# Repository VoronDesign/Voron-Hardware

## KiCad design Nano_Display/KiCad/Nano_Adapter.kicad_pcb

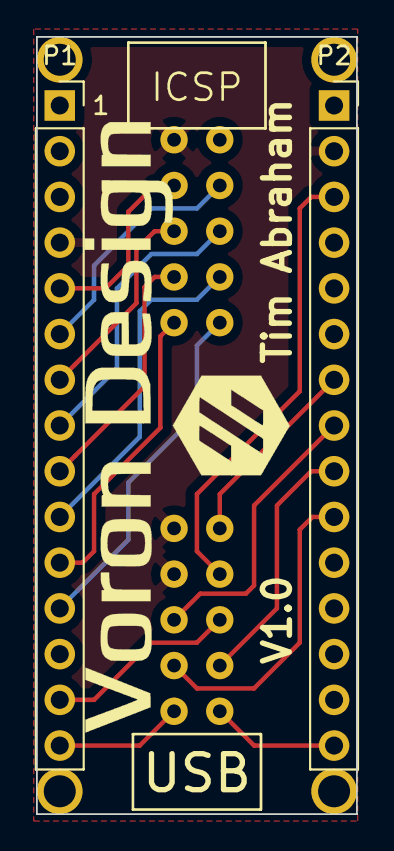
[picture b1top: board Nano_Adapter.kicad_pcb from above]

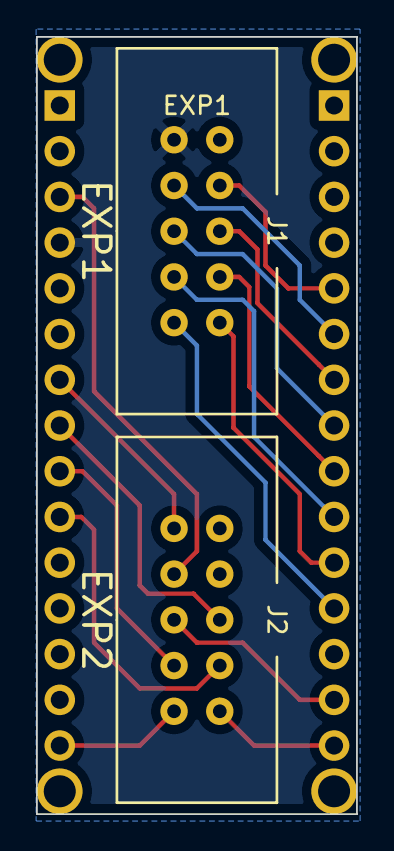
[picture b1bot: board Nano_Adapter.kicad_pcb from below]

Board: 2 copper layers, 17.8 x 43.2 mm, 8 parts (2 on the bottom side), 18 nets.

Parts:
J1: EXP1; Shrouded_2x5_pin_header
J2: EXP2; Shrouded_2x5_pin_header
P1: Digital; PinSocket_1x15_P2.54mm_Vertical
P2: Analog; PinSocket_1x15_P2.54mm_Vertical
P3, P4, P5, P6: CONN_01X01; 1pin_Nano

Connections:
+5V: J1.10, P2.4
/2: J1.7, P1.5
/3(**): J1.8, P1.6
/4: J1.5, P1.7
/5(**): J1.6, P1.8
/6(**): J1.3, P1.9
/7: J1.4, P1.10
/8: J1.1, P1.11
/9(**): J1.2, P1.12
/11(**/MOSI): J2.6, P1.14
/12(MISO): J2.1, P1.15
/13(SCK): J2.2, P2.15
/A2: J2.3, P2.10
/A3: J2.4, P2.9
/A4: J2.5, P2.8
/A5: J2.10, P2.7
/Reset: J2.8, P2.3
GND: J1.9, J2.7, J2.9, P1.4, P2.2

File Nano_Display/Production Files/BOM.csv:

"Id";"Designator";"Package";"Quantity";"Description";"Link 1";"Link 2"
1;"J1,J2";"Shrouded_2x5_pin_header";2;"2x5 pin IDC header 2.54mm Shielded";"https://www.mouser.com/ProductDetail/Wurth-Elektronik/61201021621";"https://www.amazon.com/HONJIE-10Pins-Straight-Connector-Head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"
2;"P1,P2";"PinSocket_1x15_P2.54mm_Vertical";2;"2.54mm male header pin 15 pin ";"https://www.mouser.com/ProductDetail/Gravitech/15Fx1-254mm";"https://www.amazon.com/2-54mm-Female-Single-Straight-Header/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"

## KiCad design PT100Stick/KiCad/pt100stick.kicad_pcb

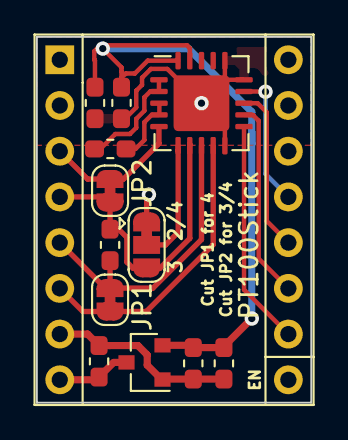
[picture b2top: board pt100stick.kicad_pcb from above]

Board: 2 copper layers, 15.2 x 20.3 mm, 13 parts (0 on the bottom side), 14 nets.

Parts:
A1: Pololu_Breakout_A4988; Pololu_Breakout-16_15.2x20.3mm
C1, C2, C3, C4, C5: 0.1uF; C_0603_1608Metric_Pad1.05x0.95mm_HandSolder
C6: 2.2uF; C_0603_1608Metric_Pad1.05x0.95mm_HandSolder
JP1: Cut for 4; SolderJumper-2_P1.3mm_Bridged_RoundedPad1.0x1.5mm
JP2: Cut for 3/4; SolderJumper-2_P1.3mm_Bridged_RoundedPad1.0x1.5mm
JP3: SolderJumper_3_Bridged12; SolderJumper-3_P1.3mm_Bridged12_RoundedPad1.0x1.5mm
R1: 402; R_0603_1608Metric_Pad1.05x0.95mm_HandSolder
U1: MAX31865ATP_; TQFN-20-1EP_5x5mm_P0.65mm_EP3.1x3.1mm
U2: MCP1799T-3302H; SOT-23

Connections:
+3V3: C2.1, C3.1, C5.1, C6.1, U1.19, U1.20, U2.2
+24V: A1.8, C4.1, U2.3
/BIAS: R1.2, U1.1, U1.2
/CS: A1.12, U1.13
/FORCE2: JP3.2, U1.6
/FORCE+: A1.3, JP2.1, U1.5
/FORCE-: A1.6, JP1.1, U1.9
/MISO: A1.10, U1.11
/MOSI: A1.13, U1.14
/RTDIN+: A1.4, C1.1, JP2.2, JP3.3, U1.7
/RTDIN-: A1.5, C1.2, JP1.2, U1.8
/SCK: A1.11, U1.12
GND: A1.7, C2.2, C3.2, C4.2, C5.2, C6.2, JP3.1, U1.10, U1.15, U1.16, U1.21, U2.1
unnamed: R1.1, U1.3, U1.4

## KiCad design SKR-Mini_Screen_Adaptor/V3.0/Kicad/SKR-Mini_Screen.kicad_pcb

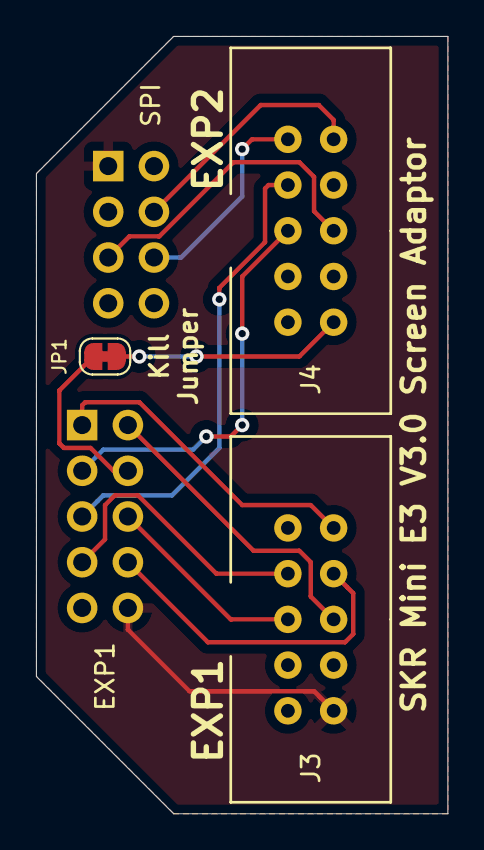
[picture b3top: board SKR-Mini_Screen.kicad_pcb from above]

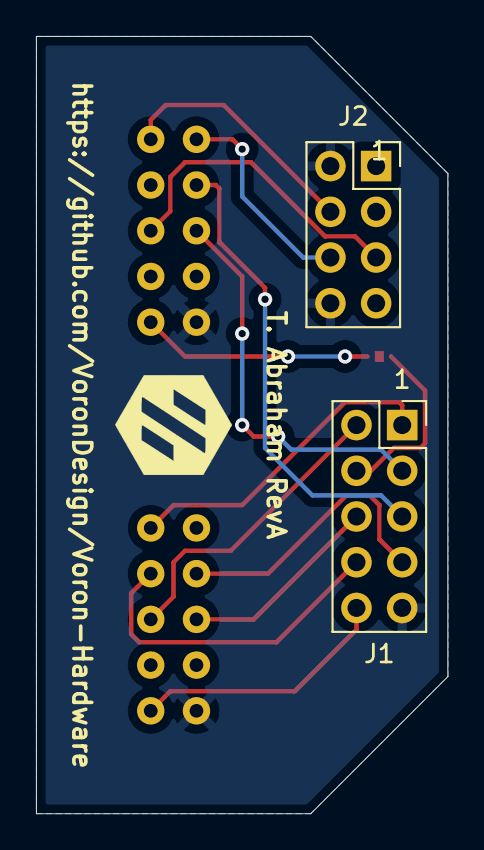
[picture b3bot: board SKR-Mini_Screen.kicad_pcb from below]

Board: 2 copper layers, 22.9 x 43.2 mm, 5 parts (2 on the bottom side), 14 nets.

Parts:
J1: Board_EXP1; PinSocket_2x05_P2.54mm_Vertical
J2: Board_SPI; PinSocket_2x04_P2.54mm_Vertical
J3: Screen_EXP1; Shrouded_2x5_pin_header
J4: Screen_EXP2; Shrouded_2x5_pin_header
JP1: Jumper_NC_Small; SolderJumper-2_P1.3mm_Bridged_RoundedPad1.0x1.5mm

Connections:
/+5V: J1.10, J2.1, J3.10
/GND: J1.9, J2.2, J2.8, J3.9, J4.9
/Kill: J4.10, JP1.2
/MISO: J2.6, J4.1
/MOSI: J2.5, J4.6
/PA9: J1.3, J4.5
/PA10: J1.5, J4.3
/PA15: J1.2, J3.6
/PB5: J1.1, J3.2
/PB8: J1.7, J3.3
/PB9: J1.6, J3.5
/PB15: J1.8, J3.4
/RST: J1.4, JP1.1
/SCK: J2.4, J4.2

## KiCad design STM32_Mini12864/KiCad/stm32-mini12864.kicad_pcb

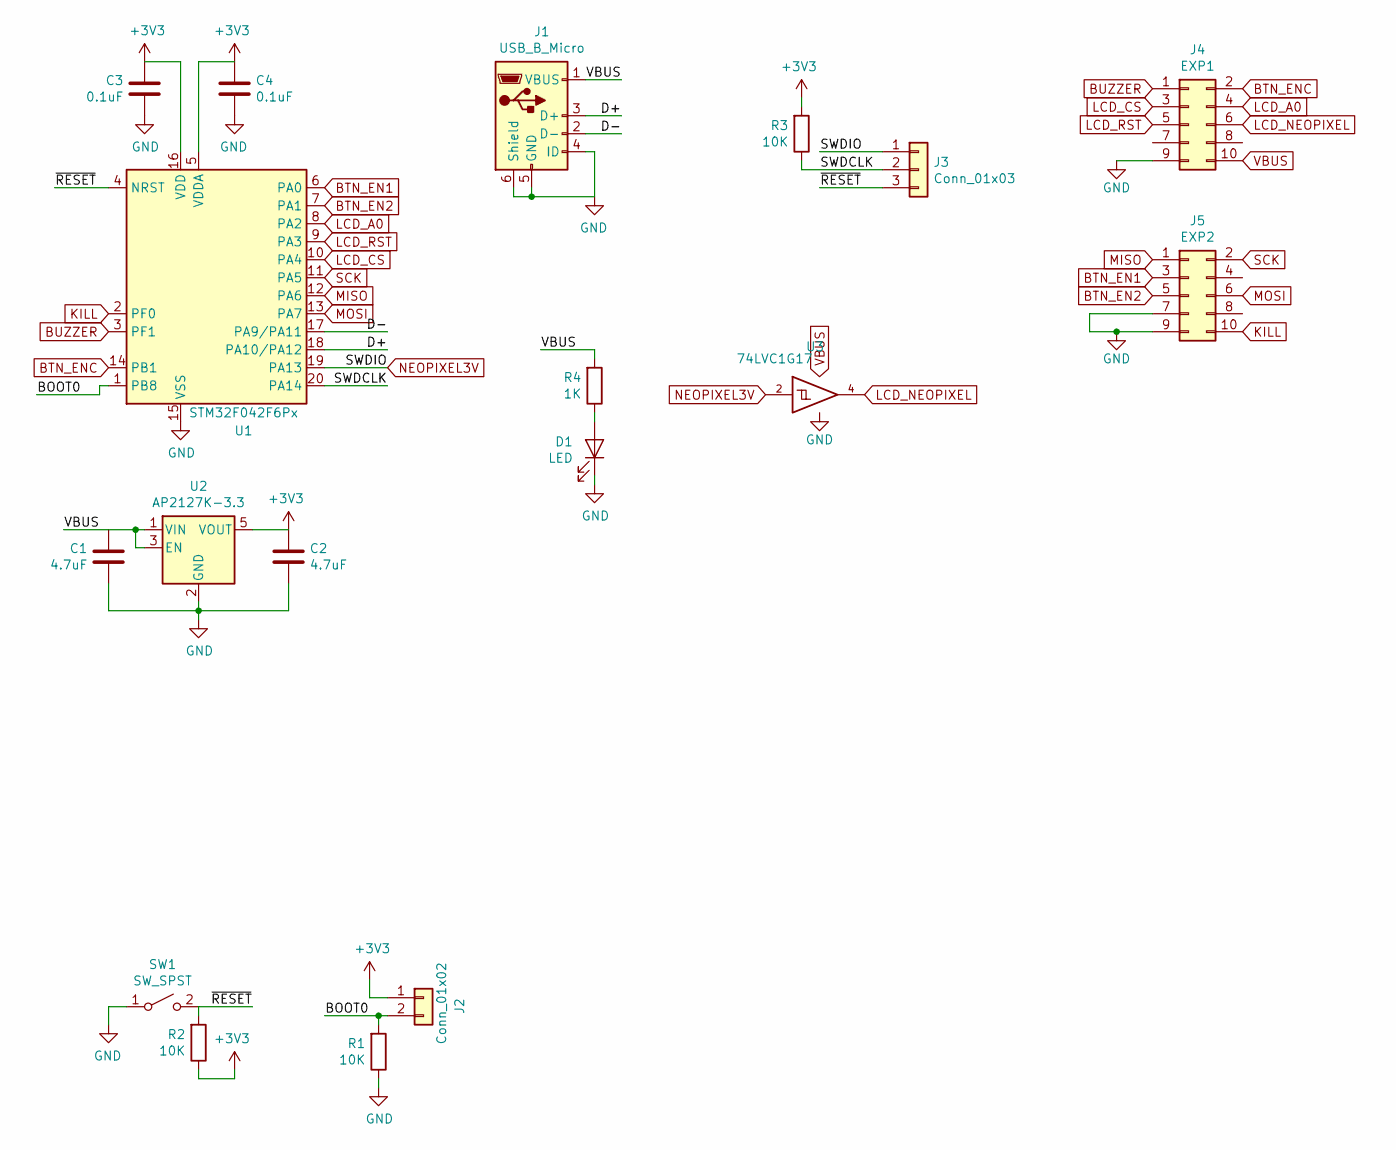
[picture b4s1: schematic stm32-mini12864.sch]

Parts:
C1, C2: 4.7uF; C_0805_2012Metric; MPN CC0805KKX5R8BB475; LCSC C1779
C3, C4: 0.1uF; C_0805_2012Metric; MPN CC0805KRX7R9BB104; LCSC C49678
D1: LED; LED_0805_2012Metric; MPN 17-215SURC/S530-A2/TR8; LCSC C84256
J1: USB_B_Micro; Molex-105017-0001-USBMicroB; MPN 1050170001
J2: Conn_01x02; PinHeader_1x02_P2.54mm_Vertical
J3: Conn_01x03; PinHeader_1x03_P2.54mm_Vertical
J4: EXP1; PinHeader_2x05_P2.54mm_Vertical_SMD_alt
J5: EXP2; PinHeader_2x05_P2.54mm_Vertical_SMD_alt
R1, R2, R3: 10K; R_0805_2012Metric; MPN RC0805JR-0710KL; LCSC C17414
R4: 1K; R_0805_2012Metric; MPN RC0805JR-071KL; LCSC C17513
SW1: SW_SPST; 2PinTactileButton
U1: STM32F042F6Px; TSSOP-20_4.4x6.5mm_P0.65mm; MPN STM32F042F6P6; LCSC C81000
U2: AP2127K-3.3; SOT-23-5; MPN AP2127K-3.3TRG1; LCSC C156285
U3: 74LVC1G17; SOT-753

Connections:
+3V3: C2.2, C3.2, C4.2, J2.1, R2.1, R3.2, U1.5 (VDDA), U1.16 (VDD), U2.5 (VOUT)
/BOOT0: J2.2, R1.2, U1.1 (PB8)
/D+: J1.3 (D+), U1.18 (PA10/PA12)
/D-: J1.2 (D-), U1.17 (PA9/PA11)
/SWDCLK: J3.2, R3.1, U1.20 (PA14)
/~RESET: J3.3, R2.2, SW1.2 (B), U1.4 (NRST)
BTN_EN1: J5.3, U1.6 (PA0)
BTN_EN2: J5.5, U1.7 (PA1)
BTN_ENC: J4.2, U1.14 (PB1)
BUZZER: J4.1, U1.3 (PF1)
GND: C1.1, C2.1, C3.1, C4.1, D1.1 (K), J1.4 (ID), J1.5 (GND), J1.6 (Shield), J4.9, J5.7, J5.9, R1.1, SW1.1 (A), U1.15 (VSS), U2.2 (GND), U3.3 (GND)
KILL: J5.10, U1.2 (PF0)
LCD_A0: J4.4, U1.8 (PA2)
LCD_CS: J4.3, U1.10 (PA4)
LCD_NEOPIXEL: J4.6, U3.4
LCD_RST: J4.5, U1.9 (PA3)
MISO: J5.1, U1.12 (PA6)
MOSI: J5.6, U1.13 (PA7)
NEOPIXEL3V: J3.1, U1.19 (PA13), U3.2
unnamed: D1.2 (A), R4.1
SCK: J5.2, U1.11 (PA5)
VBUS: C1.2, J1.1 (VBUS), J4.10, R4.2, U2.1 (VIN), U2.3 (EN), U3.5 (VCC)

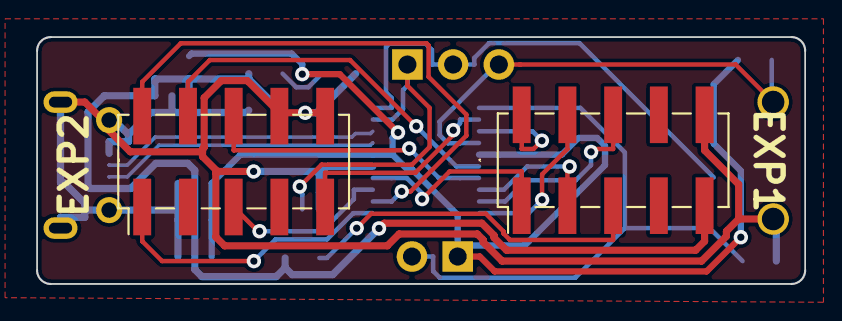
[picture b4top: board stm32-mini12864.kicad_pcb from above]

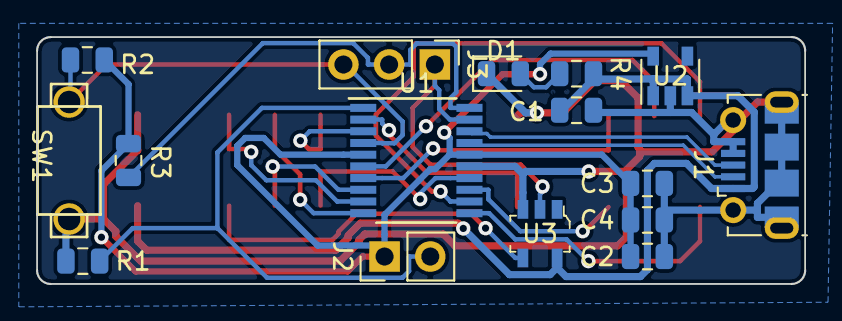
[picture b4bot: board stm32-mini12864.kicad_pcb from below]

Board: 2 copper layers, 42.7 x 13.7 mm, 18 parts (16 on the bottom side), 22 nets.

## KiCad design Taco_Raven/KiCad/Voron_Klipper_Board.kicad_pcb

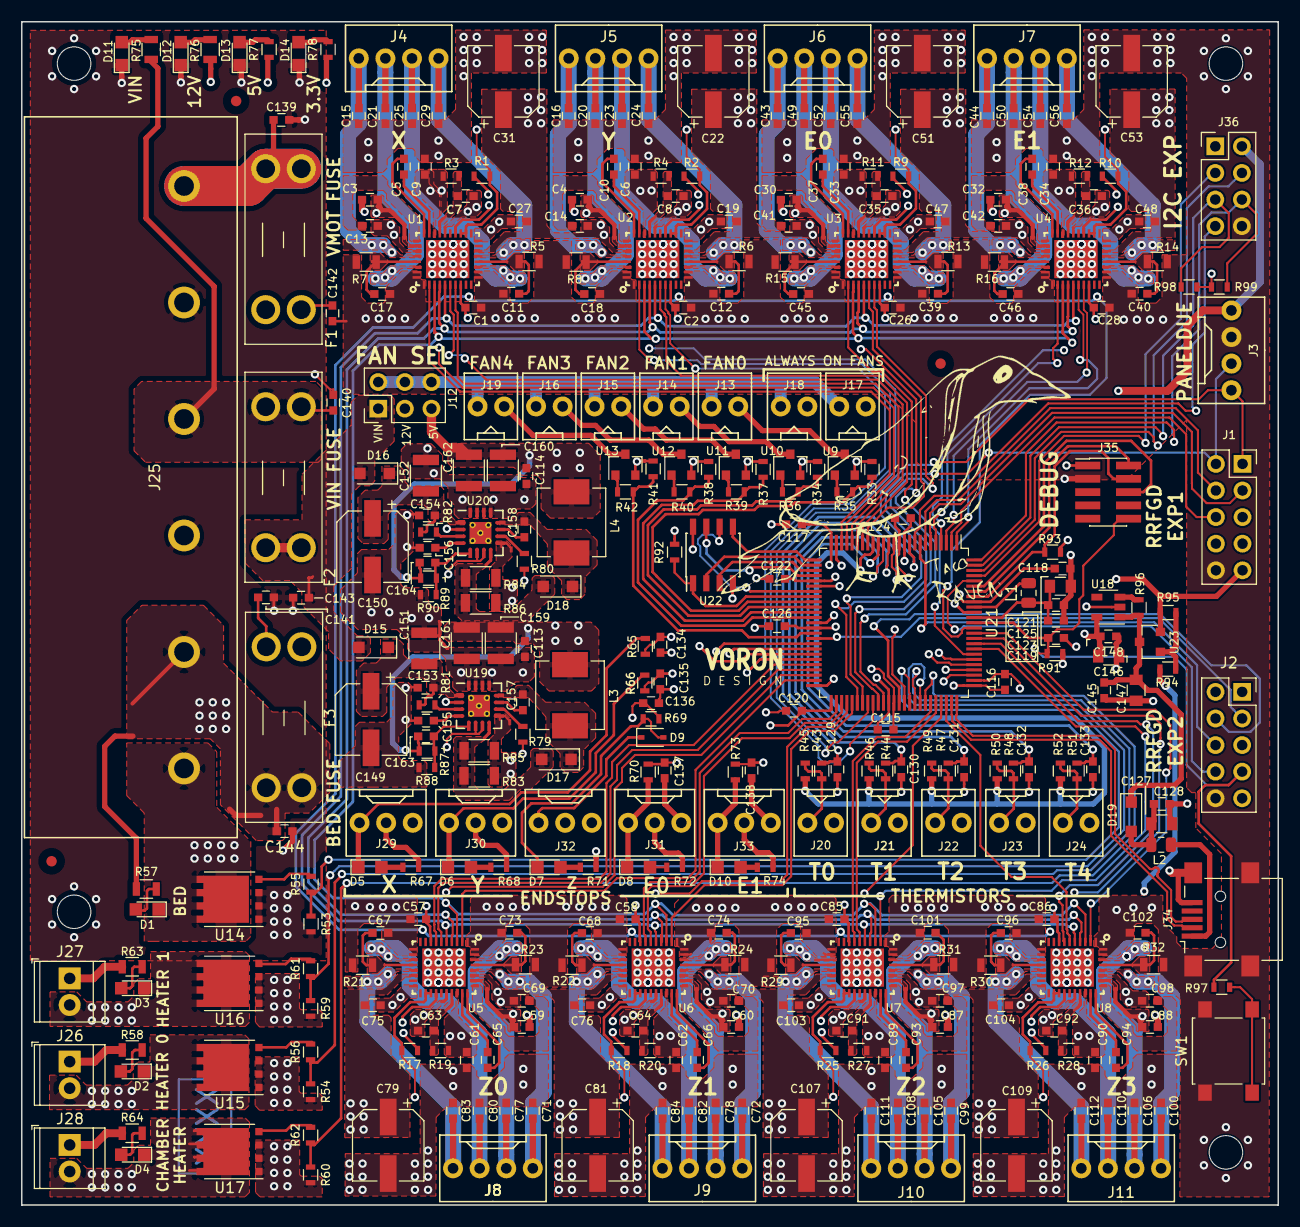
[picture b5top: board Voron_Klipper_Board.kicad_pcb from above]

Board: 4 copper layers, 120.0 x 113.0 mm, 357 parts (0 on the bottom side), 238 nets.

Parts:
C1, C2, C3, C4, C5, C6, C7, C8, C11, C12, C13, C14, C17, C18, C19, C26, C27, C28, C30, C32, C33, C34, C35, C36, C39, C40, C41, C42, C45, C46, C47, C48, C57, C58, C59, C60, C61, C62, C63, C64, C67, C68, C69, C70, C73, C74, C75, C76, C85, C86, C87, C88, C89, C90, C91, C92, C95, C96, C97, C98, C101, C102, C103, C104, C113, C114, C115, C116, C117, C118, C119, C120, C122, C124, C125, C126, C139, C140, C141, C142, C143, C144, C153, C154, C155, C156: 100nF; C_0603
C9, C10, C37, C38, C65, C66, C93, C94, C157, C158: 22nF; C_0603
C15, C16, C20, C21, C23, C24, C25, C29, C43, C44, C49, C50, C52, C54, C55, C56, C71, C72, C77, C78, C80, C82, C83, C84, C99, C100, C105, C106, C108, C110, C111, C112: 1nF; C_0603
C22, C31, C51, C53, C79, C81, C107, C109, C149, C150: 100uF; CP_Elec_6.3x7.7
C121, C127, C146, C147: 10uF; C_0805
C123, C128, C145, C148: 1uF; C_0603
C129, C130, C131, C132, C133, C134, C135, C136, C137, C138: 2.2uF; C_0603
C151, C152, C159, C160, C161, C162: 10uF; C_1210
C163: 8.2nF; C_0603
C164: 10nF; C_0603
D1, D2, D3, D4, D5, D6, D7, D8, D10: Red; LED_0805
D9: BAT43; D_SOD-323
D11, D12, D13, D14: Blue; LED_0805
D15, D16, D17, D18, D19: DB2W40300L; D_SOD-123F
F1, F2, F3: 3557-2; Fuseholder_Blade_Mini_Keystone_3568
FID1, FID2, FID3: FIDUCIAL_1MM; Fiducial_1mm_Dia_2.54mm_Outer_CopperBottom
G2: mzbot; LOGO
J1, J2: CONN_02X05; PinSocket_2x05_P2.54mm_Vertical
J3, J4, J5, J6, J7, J8, J9, J10, J11: CONN_01X04; Molex_KK_1X4
J12: CONN_02X03; PinHeader_2x03_P2.54mm_Vertical
J13, J14, J15, J16, J17, J18, J19, J20, J21, J22, J23, J24: CONN_01X02; Molex_KK_1X2
J25: CONN_01X06; 8PCV-06-006
J26, J27, J28: CONN_01X02; TerminalBlock_TE_282834-2_1x02_P2.54mm_Horizontal
J29, J30, J31, J32, J33: CONN_01X03; Molex_KK_1X3
J34: USB_MINI; USB_Mini-B_Lumberg_2486_01_Horizontal
J35: CONN_02X05; PinHeader_2x05_P1.27mm_Vertical_SMD
J36: CONN_02X04; PinHeader_2x04_P2.54mm_Vertical
L1: 10uH; L_0805_2012Metric
L2: Ferrite_0805; L_0805_2012Metric
L3, L4: 10uH; L_Vishay_IHLP-2525
MH1, MH2, MH3, MH4: MountingHole; MountingHole_3.2mm_M3_DIN965
R1, R2, R9, R10, R17, R18, R25, R26, R33, R34, R37, R38, R41, R53, R54, R59, R60, R65, R66, R69, R70, R73, R91, R92, R93: 10.0K; R_0603
R3, R4, R11, R12, R19, R20, R27, R28: 10R; R_0603
R5, R6, R7, R8, R13, R14, R15, R16, R21, R22, R23, R24, R29, R30, R31, R32: 0R11; R_0805
R35, R36, R39, R40, R42, R43, R44, R47, R48, R51, R67, R68, R71, R72, R74, R77: 1.00K; R_0603
R45, R46, R49, R50, R52, R98, R99: 4.70K; R_0603
R55, R56, R61, R62, R78: 180; R_0603
R57, R58, R63, R64, R75, R76: 6.80K; R_0805
R79, R80: 0R; R_0603
R81: 200K; R_0603
R82, R94, R95, R96: 100K; R_0603
R83, R85: 0.10; R_1206
R84, R86: 0.130; R_1206
R87: 10.5K; R_0603
R88: 750; R_0603
R89: 3.48K; R_0603
R90: 681; R_0603
R97: 330; R_0603
SW1: SW_Push; SW_SPST_B3S-1000
U1, U2, U3, U4, U5, U6, U7, U8: TMC2130; QFN36_0.5_5.0X6.0
U9, U10, U11, U12, U13, U23: PMV40UN; SOT-23
U14, U15, U16, U17: CSD18532; VSONP-8-1EP_5x6_P1.27mm
U18: AP2112-3.3; SOT-23-5
U19, U20: A4403; WQFN-16-1EP_4x4mm_P0.65mm_EP2.1x2.1mm_ThermalVias
U21: ATSAMD51; TQFP-100_14x14mm_P0.5mm
U22: SPIFLASH_SOIC8; SOIC-8_3.9x4.9mm_Pitch1.27mm

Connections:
+3.3V: C1.2, C2.2, C26.2, C28.2, C57.2, C58.2, C85.2, C86.2, C115.2, C116.2, C117.2, C118.2, C120.2, C122.2, C124.2, C126.2, C146.2, C148.2, J29.2, J30.2, J31.2, J33.2, J35.1, J36.1, R1.1, R2.1, R9.1, R10.1, R17.1, R18.1, R25.1, R26.1, R67.2, R68.2, R71.2, R72.2, R74.2, R78.1, R91.1, R92.1, R93.1, R98.1, R99.1, U1.8, U2.8, U3.8, U4.8, U5.8, U6.8, U7.8, U8.8, U18.5, U21.12, U21.25, U21.30, U21.39, U21.51, U21.63, U21.77, U21.92, U22.8
+5V: C3.2, C4.2, C5.2, C6.2, C30.2, C32.2, C33.2, C34.2, C59.2, C60.2, C61.2, C62.2, C87.2, C88.2, C89.2, C90.2, C114.2, C160.1, C162.1, C164.2, J1.9, J3.4, J12.5, J36.2, L4.2, R3.1, R4.1, R11.1, R12.1, R19.1, R20.1, R27.1, R28.1, R77.1, R89.1, R95.1, U1.26, U1.30, U2.26, U2.30, U3.26, U3.30, U4.26, U4.30, U5.26, U5.30, U6.26, U6.30, U7.26, U7.30, U8.26, U8.30, U23.2
+12V: C113.2, C159.1, C161.1, C163.2, J12.3, J32.2, L3.2, R76.1, R87.1, R94.2
+VIN: C140.2, C141.2, F2.1, F3.1, J25.3, R75.1
+VIN_FUSED: C143.2, D15.2, D16.2, F2.2, J12.1, J26.1, J27.1, J28.1, R58.1, R63.1, R64.1
+V_FAN: J12.2, J12.4, J12.6, J13.2, J14.2, J15.2, J16.2, J17.2, J18.2, J19.2
BED: R53.1, R55.1, U21.66
BED_SWITCH: D1.1, J25.6, U14.3
D+: J34.3, U21.75
D-: J34.2, U21.74
DIAG_E0: R9.2, U3.20, U3.21, U21.61
DIAG_E1: R10.2, U4.20, U4.21, U21.4
DIAG_X: R1.2, U1.20, U1.21, U21.22
DIAG_Y: R2.2, U2.20, U2.21, U21.58
DIAG_Z0: R17.2, U5.20, U5.21, U21.48
DIAG_Z1: R18.2, U6.20, U6.21, U21.54
DIAG_Z2: R25.2, U7.20, U7.21, U21.72
DIAG_Z3: R26.2, U8.20, U8.21, U21.85
DIR_E0: U3.7, U21.60
DIR_E1: U4.7, U21.3
DIR_X: U1.7, U21.21
DIR_Y: U2.7, U21.45
DIR_Z0: U5.7, U21.46
DIR_Z1: U6.7, U21.52
DIR_Z2: U7.7, U21.70
DIR_Z3: U8.7, U21.84
E0_OA1: C49.2, J6.3, U3.34
E0_OA2: C43.2, J6.4, U3.32
E0_OB1: C52.2, J6.2, U3.13
E0_OB2: C55.2, J6.1, U3.15
E1_OA1: C50.2, J7.3, U4.34
E1_OA2: C44.2, J7.4, U4.32
E1_OB1: C54.2, J7.2, U4.13
E1_OB2: C56.2, J7.1, U4.15
ENDSTOP_E0: C137.2, R70.2, U21.80
ENDSTOP_E1: C138.2, R73.2, U21.81
ENDSTOP_X: C134.2, R65.2, U21.65
ENDSTOP_Y: C135.2, R66.2, U21.78
EXP_I2C_INT: J36.4, U21.98
EXP_I2C_OSCK: J36.3, U21.97
EXP_I2C_RST: J36.7, U21.9
EXP_I2C_SCL: J36.6, R99.2, U21.100
EXP_I2C_SDA: J36.5, R98.2, U21.99
FAN0: R33.1, R35.2, U21.34
FAN1: R34.1, R36.2, U21.35
FAN2: R37.1, R39.2, U21.36
FAN3: R38.1, R40.2, U21.37
FAN4: R41.1, R42.2, U21.40
FLASH_CS: R92.2, U21.33, U22.1
FLASH_IO0: U21.26, U22.5
FLASH_IO1: U21.27, U22.2
FLASH_IO2: U21.28, U22.3
FLASH_IO3: U21.29, U22.7
FLASH_SCK: U21.32, U22.6
GND: C1.1, C2.1, C3.1, C4.1, C5.1, C6.1, C7.1, C8.1, C11.1, C12.1, C15.1, C16.1, C17.1, C18.1, C19.1, C20.1, C21.1, C22.2, C23.1, C24.1, C25.1, C26.1, C27.1, C28.1, C29.1, C30.1, C31.2, C32.1, C33.1, C34.1, C35.1, C36.1, C39.1, C40.1, C43.1, C44.1, C45.1, C46.1, C47.1, C48.1, C49.1, C50.1, C51.2, C52.1, C53.2, C54.1, C55.1, C56.1, C57.1, C58.1, C59.1, C60.1, C61.1, C62.1, C63.1, C64.1, C67.1, C68.1, C71.1, C72.1, C73.1, C74.1, C75.1, C76.1, C77.1, C78.1, C79.2, C80.1, C81.2, C82.1, C83.1, C84.1, C85.1, C86.1, C87.1, C88.1, C89.1, C90.1, C91.1, C92.1, C95.1, C96.1, C99.1, C100.1, C101.1, C102.1, C103.1, C104.1, C105.1, C106.1, C107.2, C108.1, C109.2, C110.1, C111.1, C112.1, C113.1, C114.1, C115.1, C116.1, C117.1, C118.1, C119.1, C120.1, C121.1, C122.1, C123.1, C124.1, C125.1, C126.1, C127.1, C128.1, C129.1, C130.1, C131.1, C132.1, C133.1, C134.1, C135.1, C136.1, C137.1, C138.1, C139.1, C140.1, C141.1, C142.1, C143.1, C144.1, C145.1, C146.1, C147.1, C148.1, C149.2, C150.2, C151.2, C152.2, C153.1, C154.1, C155.1, C156.1, C159.2, C160.2, C161.2, C162.2, D11.1, D12.1, D13.1, D14.1, J1.10, J2.10, J3.3, J17.1, J18.1, J20.2, J21.2, J22.2, J23.2, J24.2, J25.2, J25.4, J29.3, J30.3, J31.3, J32.3, J33.3, J34.5, J34.6, J35.3, J36.8, R5.2, R6.2, R7.2, R8.2, R13.2, R14.2, R15.2, R16.2, R21.2, R22.2, R23.2, R24.2, R29.2, R30.2, R31.2, R32.2, R33.2, R34.2, R37.2, R38.2, R41.2, R53.2, R54.2, R59.2, R60.2, R79.2, R80.2, R83.2, R84.2, R85.2, R86.2, R88.2, R90.2, SW1.1, U1.1, U1.11, U1.12, U1.18, U1.24, U1.35, U1.36, U1.37, U2.1, U2.11, U2.12, U2.18, U2.24, U2.35, U2.36, U2.37, U3.1, U3.11, U3.12, U3.18, U3.24, U3.35, U3.36, U3.37, U4.1, U4.11, U4.12, U4.18, U4.24, U4.35, U4.36, U4.37, U5.1, U5.11, U5.12, U5.18, U5.24, U5.35, U5.36, U5.37, U6.1, U6.11, U6.12, U6.18, U6.24, U6.35, U6.36, U6.37, U7.1, U7.11, U7.12, U7.18, U7.24, U7.35, U7.36, U7.37, U8.1, U8.11, U8.12, U8.18, U8.24, U8.35, U8.36, U8.37, U9.2, U10.2, U11.2, U12.2, U13.2, U14.1, U15.1, U16.1, U17.1, U18.2, U19.2, U19.6, U19.7, U19.9, U19.13, U19.14, U19.15, U19.16, U19.17, U20.2, U20.6, U20.7, U20.9, U20.13, U20.14, U20.15, U20.16, U20.17, U21.11, U21.24, U21.31, U21.38, U21.50, U21.62, U21.76, U21.90, U22.4
HEATED_CHAMBER: R60.1, R62.1, U21.69
HOTEND0: R54.1, R56.1, U21.67
HOTEND1: R59.1, R61.1, U21.68
unnamed: C7.2, R3.2, U1.25
unnamed: C8.2, R4.2, U2.25
unnamed: C9.1, U1.28
unnamed: C9.2, U1.27
unnamed: C10.1, U2.28
unnamed: C10.2, U2.27
unnamed: C11.2, R5.1, U1.14
unnamed: C12.2, R6.1, U2.14
unnamed: C13.1, U1.29
unnamed: C14.1, U2.29
unnamed: C17.2, R7.1, U1.33
unnamed: C18.2, R8.1, U2.33
unnamed: C35.2, R11.2, U3.25
unnamed: C36.2, R12.2, U4.25
unnamed: C37.1, U3.28
unnamed: C37.2, U3.27
unnamed: C38.1, U4.28
unnamed: C38.2, U4.27
unnamed: C39.2, R13.1, U3.14
unnamed: C40.2, R14.1, U4.14
unnamed: C41.1, U3.29
unnamed: C42.1, U4.29
unnamed: C45.2, R15.1, U3.33
unnamed: C46.2, R16.1, U4.33
unnamed: C63.2, R19.2, U5.25
unnamed: C64.2, R20.2, U6.25
unnamed: C65.1, U5.28
unnamed: C65.2, U5.27
unnamed: C66.1, U6.28
unnamed: C66.2, U6.27
unnamed: C67.2, R21.1, U5.14
unnamed: C68.2, R22.1, U6.14
unnamed: C69.1, U5.29
unnamed: C70.1, U6.29
unnamed: C73.2, R23.1, U5.33
unnamed: C74.2, R24.1, U6.33
unnamed: C91.2, R27.2, U7.25
unnamed: C92.2, R28.2, U8.25
unnamed: C93.1, U7.28
unnamed: C93.2, U7.27
unnamed: C94.1, U8.28
unnamed: C94.2, U8.27
unnamed: C95.2, R29.1, U7.14
unnamed: C96.2, R30.1, U8.14
unnamed: C97.1, U7.29
unnamed: C98.1, U8.29
unnamed: C101.2, R31.1, U7.33
unnamed: C102.2, R32.1, U8.33
unnamed: C121.2, C123.2, C125.2, L1.1, U21.89
unnamed: C145.2, C147.2, D19.1, R96.2, U18.1, U23.3
unnamed: C149.1, C151.1, C153.2, D15.1, R81.1, U19.1
unnamed: C150.1, C152.1, C154.2, D16.1, R82.1, U20.1
unnamed: C155.2, U19.4
unnamed: C156.2, U20.4
unnamed: C157.1, U19.11
unnamed: C157.2, D17.1, L3.1, U19.12
unnamed: C158.1, U20.11
unnamed: C158.2, D18.1, L4.1, U20.12
unnamed: C163.1, R87.2, R88.1, U19.5
unnamed: C164.1, R89.2, R90.1, U20.5
unnamed: D1.2, R57.2
unnamed: D2.1, J26.2, U15.3
unnamed: D2.2, R58.2
unnamed: D3.1, J27.2, U16.3
unnamed: D3.2, R63.2
unnamed: D4.1, J28.2, U17.3
unnamed: D4.2, R64.2
unnamed: D5.1, J29.1, R65.1
unnamed: D5.2, R67.1
unnamed: D6.1, J30.1, R66.1
unnamed: D6.2, R68.1
unnamed: D7.1, D9.2, R69.1
unnamed: D7.2, R71.1
unnamed: D8.1, J31.1, R70.1
unnamed: D8.2, R72.1
unnamed: D9.1, J32.1
unnamed: D10.1, J33.1, R73.1
unnamed: D10.2, R74.1
unnamed: D11.2, R75.2
unnamed: D12.2, R76.2
unnamed: D13.2, R77.2
unnamed: D14.2, R78.2
unnamed: D17.2, R83.1, R85.1, U19.8
unnamed: D18.2, R84.1, R86.1, U20.8
unnamed: J13.1, U9.3
unnamed: J14.1, U10.3
unnamed: J15.1, U11.3
unnamed: J16.1, U12.3
unnamed: J19.1, U13.3
unnamed: J20.1, R43.1, R45.2
unnamed: J21.1, R44.1, R46.2
unnamed: J22.1, R47.1, R49.2
unnamed: J23.1, R48.1, R50.2
unnamed: J24.1, R51.1, R52.2
unnamed: J34.1, L2.1
unnamed: L1.2, U21.91
unnamed: R35.1, U9.1
unnamed: R36.1, U10.1
unnamed: R39.1, U11.1
unnamed: R40.1, U12.1
unnamed: R42.1, U13.1
unnamed: R55.2, U14.2
unnamed: R56.2, U15.2
unnamed: R61.2, U16.2
unnamed: R62.2, U17.2
unnamed: R79.1, U19.10
unnamed: R80.1, U20.10
unnamed: R81.2, U19.3
unnamed: R82.2, U20.3
unnamed: R94.1, R95.2, U23.1
unnamed: R96.1, U18.3
unnamed: R97.2, SW1.2
PD_RX_RRFGD_BUZ: J1.2, J3.2, U21.56
PD_TX_RRFGD_BTN_ENC: J1.1, J3.1, U21.57
RESETN: C119.2, J2.7, J35.10, R91.2, R97.1, U21.88
RRFGD_BTN_EN1: J2.4, U21.64
RRFGD_BTN_EN2: J2.6, U21.8
RRFGD_LCD4: J1.6, U21.2
RRFGD_LCDE: J1.4, U21.7
RRFGD_LCDRS: J1.3, U21.6
RRFGD_SDCSEL: J2.3, U21.41
RRFGD_SDDET: J2.8, U21.96
SPI_CLK: J2.1, U1.3, U2.3, U3.3, U4.3, U5.3, U6.3, U7.3, U8.3, U21.43
SPI_CS_E0: U3.2, U21.82
SPI_CS_E1: U4.2, U21.5
SPI_CS_X: U1.2, U21.23
SPI_CS_Y: U2.2, U21.59
SPI_CS_Z0: U5.2, U21.49
SPI_CS_Z1: U6.2, U21.55
SPI_CS_Z2: U7.2, U21.83
SPI_CS_Z3: U8.2, U21.86
SPI_SDI: J2.2, U1.4, U2.4, U3.4, U4.4, U5.4, U6.4, U7.4, U8.4, U21.42
SPI_SDO: J2.5, U1.5, U2.5, U3.5, U4.5, U5.5, U6.5, U7.5, U8.5, U21.44
STEP_E0: U3.6, U21.18
STEP_E1: U4.6, U21.1
STEP_X: U1.6, U21.20
STEP_Y: U2.6, U21.19
STEP_Z0: U5.6, U21.47
STEP_Z1: U6.6, U21.53
STEP_Z2: U7.6, U21.71
STEP_Z3: U8.6, U21.73
SWCLK: J35.4, R93.2, U21.93
SWDIO: J35.2, U21.94
SWO: J35.6, U21.95
T0: C129.2, R43.2, U21.10
T1: C130.2, R44.2, U21.13
T2: C131.2, R47.2, U21.14
T3: C132.2, R48.2, U21.15
T4: C133.2, R51.2, U21.16
TMC_EN: U1.22, U2.22, U3.22, U4.22, U5.22, U6.22, U7.22, U8.22, U21.87
VBED_FUSED: C144.2, F3.2, J25.5, R57.1
VBUS: C127.2, C128.2, D19.2, L2.2
VMOT: C139.2, F1.1, J25.1
VMOT_FUSED: C13.2, C14.2, C19.2, C22.1, C27.2, C31.1, C41.2, C42.2, C47.2, C48.2, C51.1, C53.1, C69.2, C70.2, C75.2, C76.2, C79.1, C81.1, C97.2, C98.2, C103.2, C104.2, C107.1, C109.1, C142.2, F1.2, U1.16, U1.31, U2.16, U2.31, U3.16, U3.31, U4.16, U4.31, U5.16, U5.31, U6.16, U6.31, U7.16, U7.31, U8.16, U8.31
VREF: R45.1, R46.1, R49.1, R50.1, R52.1, U21.17
X_OA1: C21.2, J4.3, U1.34
X_OA2: C15.2, J4.4, U1.32
X_OB1: C25.2, J4.2, U1.13
X_OB2: C29.2, J4.1, U1.15
Y_OA1: C20.2, J5.3, U2.34
Y_OA2: C16.2, J5.4, U2.32
Y_OB1: C23.2, J5.2, U2.13
Y_OB2: C24.2, J5.1, U2.15
Z0_OA1: C77.2, J8.3, U5.34
Z0_OA2: C71.2, J8.4, U5.32
Z0_OB1: C80.2, J8.2, U5.13
Z0_OB2: C83.2, J8.1, U5.15
Z1_OA1: C78.2, J9.3, U6.34
Z1_OA2: C72.2, J9.4, U6.32
Z1_OB1: C82.2, J9.2, U6.13
Z1_OB2: C84.2, J9.1, U6.15
Z2_OA1: C105.2, J10.3, U7.34
Z2_OA2: C99.2, J10.4, U7.32
Z2_OB1: C108.2, J10.2, U7.13
Z2_OB2: C111.2, J10.1, U7.15
Z3_OA1: C106.2, J11.3, U8.34
Z3_OA2: C100.2, J11.4, U8.32
Z3_OB1: C110.2, J11.2, U8.13
Z3_OB2: C112.2, J11.1, U8.15
Z_PROBE: C136.2, R69.2, U21.79

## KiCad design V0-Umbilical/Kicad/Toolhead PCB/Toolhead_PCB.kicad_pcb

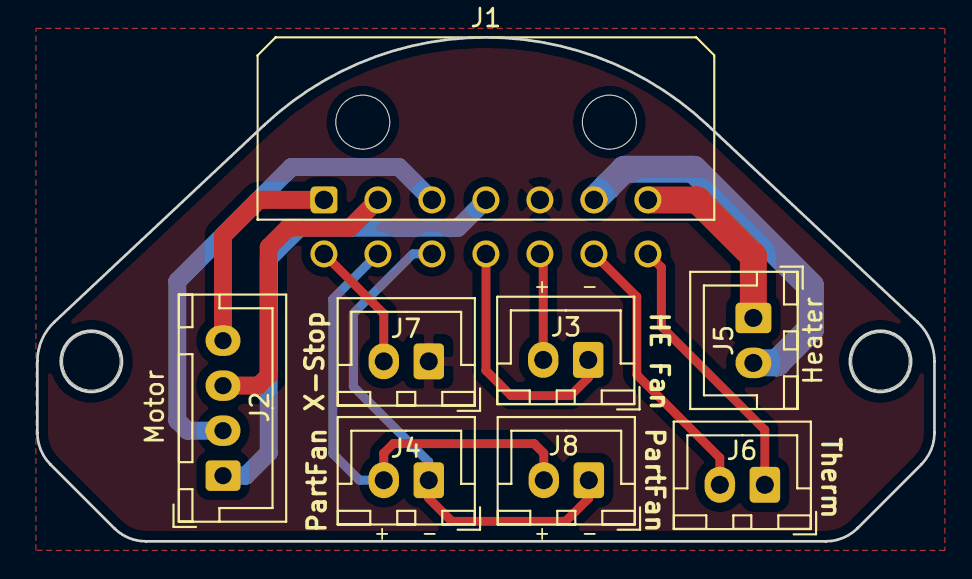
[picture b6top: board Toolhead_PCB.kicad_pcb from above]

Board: 2 copper layers, 49.8 x 28.0 mm, 10 parts (0 on the bottom side), 14 nets.

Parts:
H1, H2: MountingHole; MountingHole_3.2mm_M3
J1: Conn_02x07_Top_Bottom; Molex_Micro-Fit_3.0_43045-1400_2x07_P3.00mm_Horizontal
J2: Motor; JST_XH_B4B-XH-A_1x04_P2.50mm_Vertical
J3: Hotend Fan; JST_XH_B2B-XH-A_1x02_P2.50mm_Vertical
J4, J8: Part Cooling Fan; JST_XH_B2B-XH-A_1x02_P2.50mm_Vertical
J5: Heater; JST_XH_B2B-XH-A_1x02_P2.50mm_Vertical
J6: Thermistor; JST_XH_B2B-XH-A_1x02_P2.50mm_Vertical
J7: X-Endstop; JST_XH_B2B-XH-A_1x02_P2.50mm_Vertical

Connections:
/Endstop_Sig: J1.8, J7.2
/Heater1: J1.7, J5.1
/Heater2: J1.6, J5.2
/Hotend_Fan+: J1.12, J3.2
/Hotend_Fan-: J1.11, J3.1
/Motor_A1: J1.1, J2.4
/Motor_A2: J1.2, J2.3
/Motor_B1: J1.3, J2.2
/Motor_B2: J1.4, J2.1
/PartFan+: J1.9, J4.2, J8.2
/PartFan-: J1.10, J4.1, J8.1
/Thermistor_1: J1.13, J6.2
/Thermistor_2: J1.14, J6.1
GND: J1.5, J7.1

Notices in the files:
PT100Stick/KiCad/pt100stick.kicad_pcb:
licensed under GPL3
